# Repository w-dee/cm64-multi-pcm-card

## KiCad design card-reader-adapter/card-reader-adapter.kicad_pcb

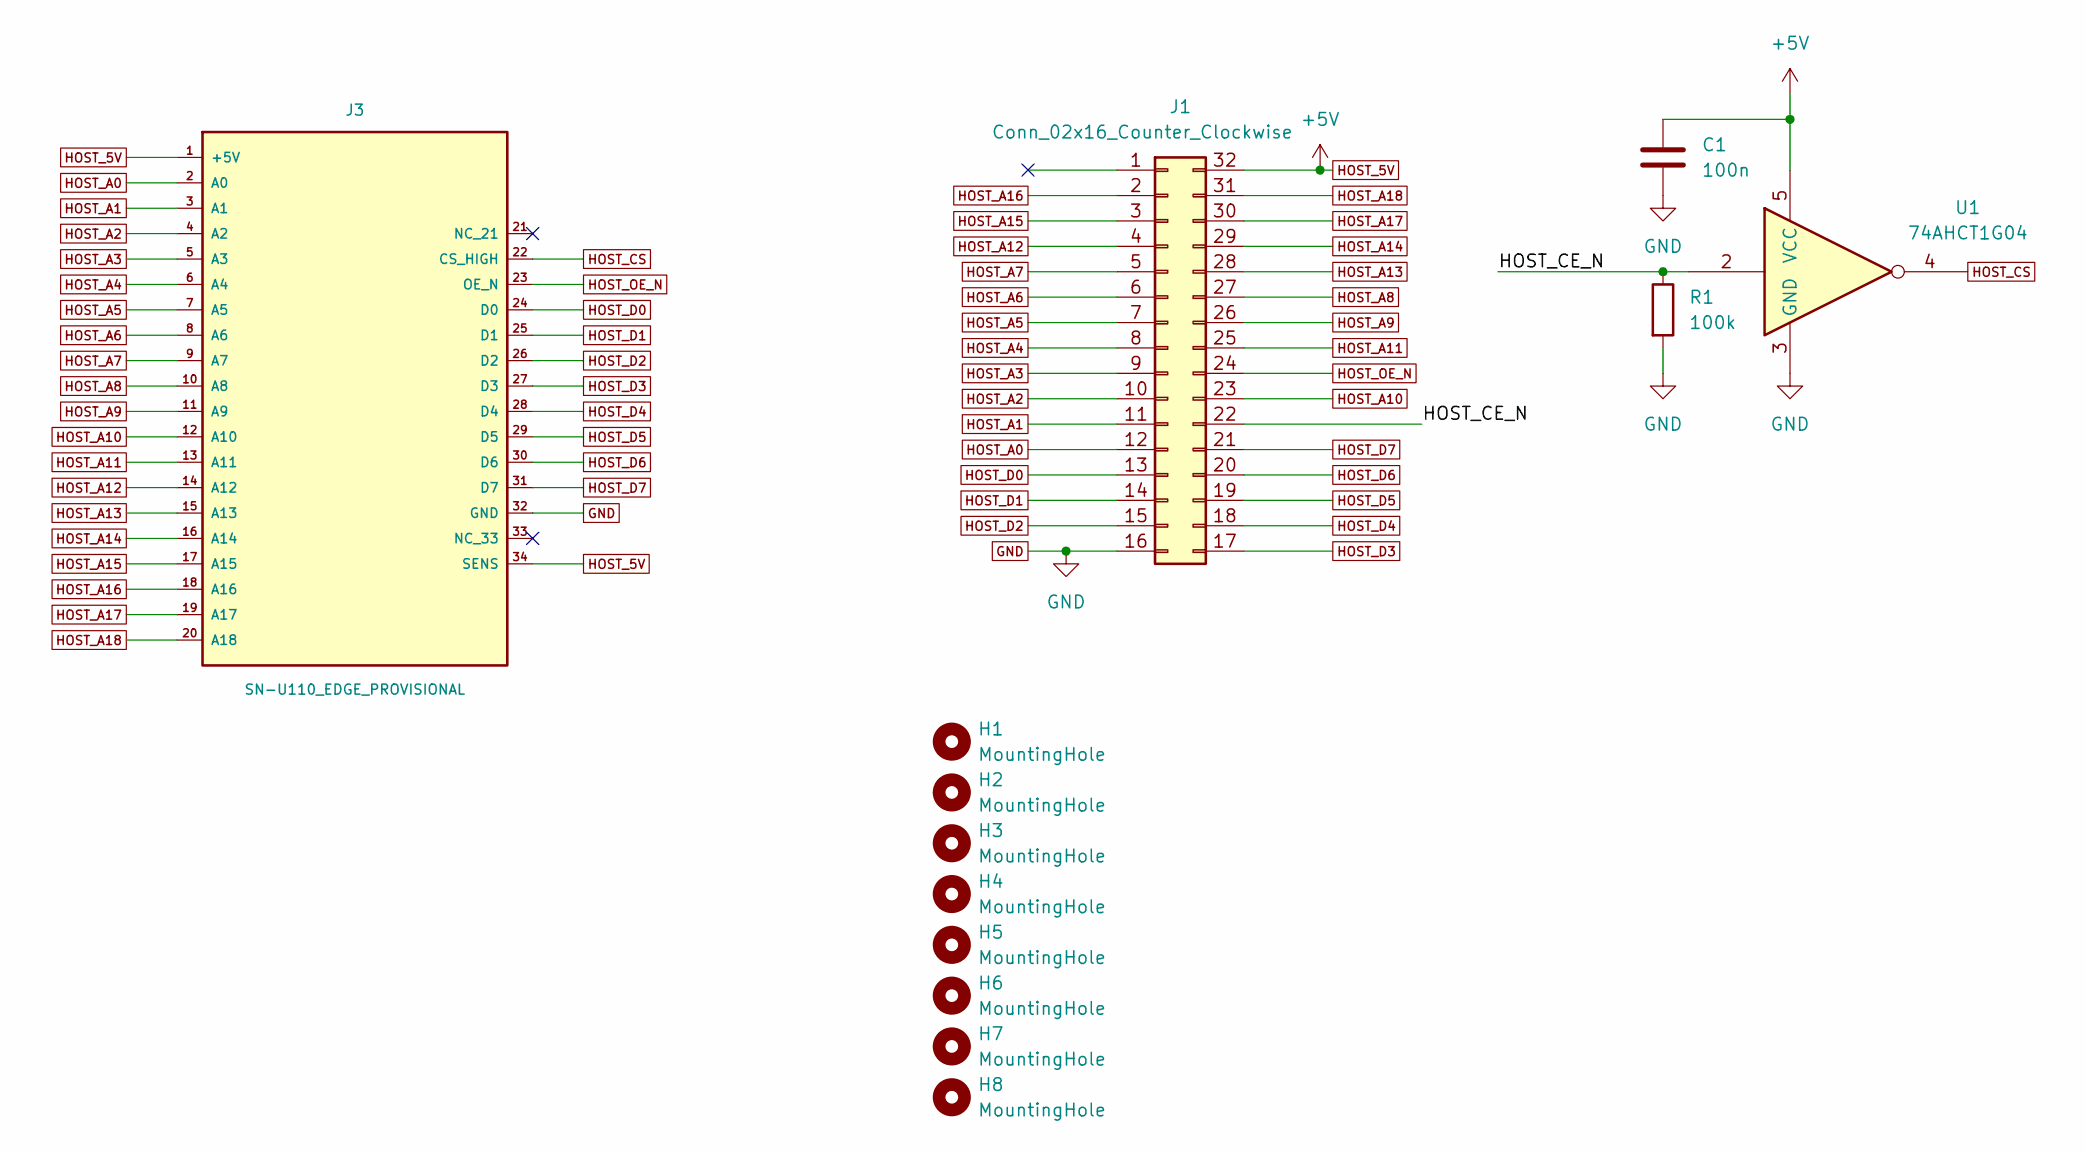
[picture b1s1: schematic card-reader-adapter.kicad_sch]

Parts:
C1: 100n; C_0603_1608Metric_Pad1.08x0.95mm_HandSolder
H1, H2, H3, H4, H5, H6, H7, H8: MountingHole; MountingHole_3.2mm_M3
J1: Conn_02x16_Counter_Clockwise; DIP-32_W15.24mm_Socket_LongPads
J3: SN-U110_EDGE_PROVISIONAL; pogo-pins-SN-U110; MPN SN-U110_EDGE_PROVISIONAL
R1: 100k; R_0603_1608Metric_Pad0.98x0.95mm_HandSolder
U1: 74AHCT1G04; SOT-23-5_HandSoldering

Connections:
/HOST_CE_N: J1.22, R1.1, U1.2
GND: C1.2, J1.16, J3.32 (GND), R1.2, U1.3 (GND)
HOST_5V: C1.1, J1.32, J3.1 (+5V), J3.34 (SENS), U1.5 (VCC)
HOST_A0: J1.12, J3.2 (A0)
HOST_A1: J1.11, J3.3 (A1)
HOST_A2: J1.10, J3.4 (A2)
HOST_A3: J1.9, J3.5 (A3)
HOST_A4: J1.8, J3.6 (A4)
HOST_A5: J1.7, J3.7 (A5)
HOST_A6: J1.6, J3.8 (A6)
HOST_A7: J1.5, J3.9 (A7)
HOST_A8: J1.27, J3.10 (A8)
HOST_A9: J1.26, J3.11 (A9)
HOST_A10: J1.23, J3.12 (A10)
HOST_A11: J1.25, J3.13 (A11)
HOST_A12: J1.4, J3.14 (A12)
HOST_A13: J1.28, J3.15 (A13)
HOST_A14: J1.29, J3.16 (A14)
HOST_A15: J1.3, J3.17 (A15)
HOST_A16: J1.2, J3.18 (A16)
HOST_A17: J1.30, J3.19 (A17)
HOST_A18: J1.31, J3.20 (A18)
HOST_CS: J3.22 (CS_HIGH), U1.4
HOST_D0: J1.13, J3.24 (D0)
HOST_D1: J1.14, J3.25 (D1)
HOST_D2: J1.15, J3.26 (D2)
HOST_D3: J1.17, J3.27 (D3)
HOST_D4: J1.18, J3.28 (D4)
HOST_D5: J1.19, J3.29 (D5)
HOST_D6: J1.20, J3.30 (D6)
HOST_D7: J1.21, J3.31 (D7)
HOST_OE_N: J1.24, J3.23 (OE_N)

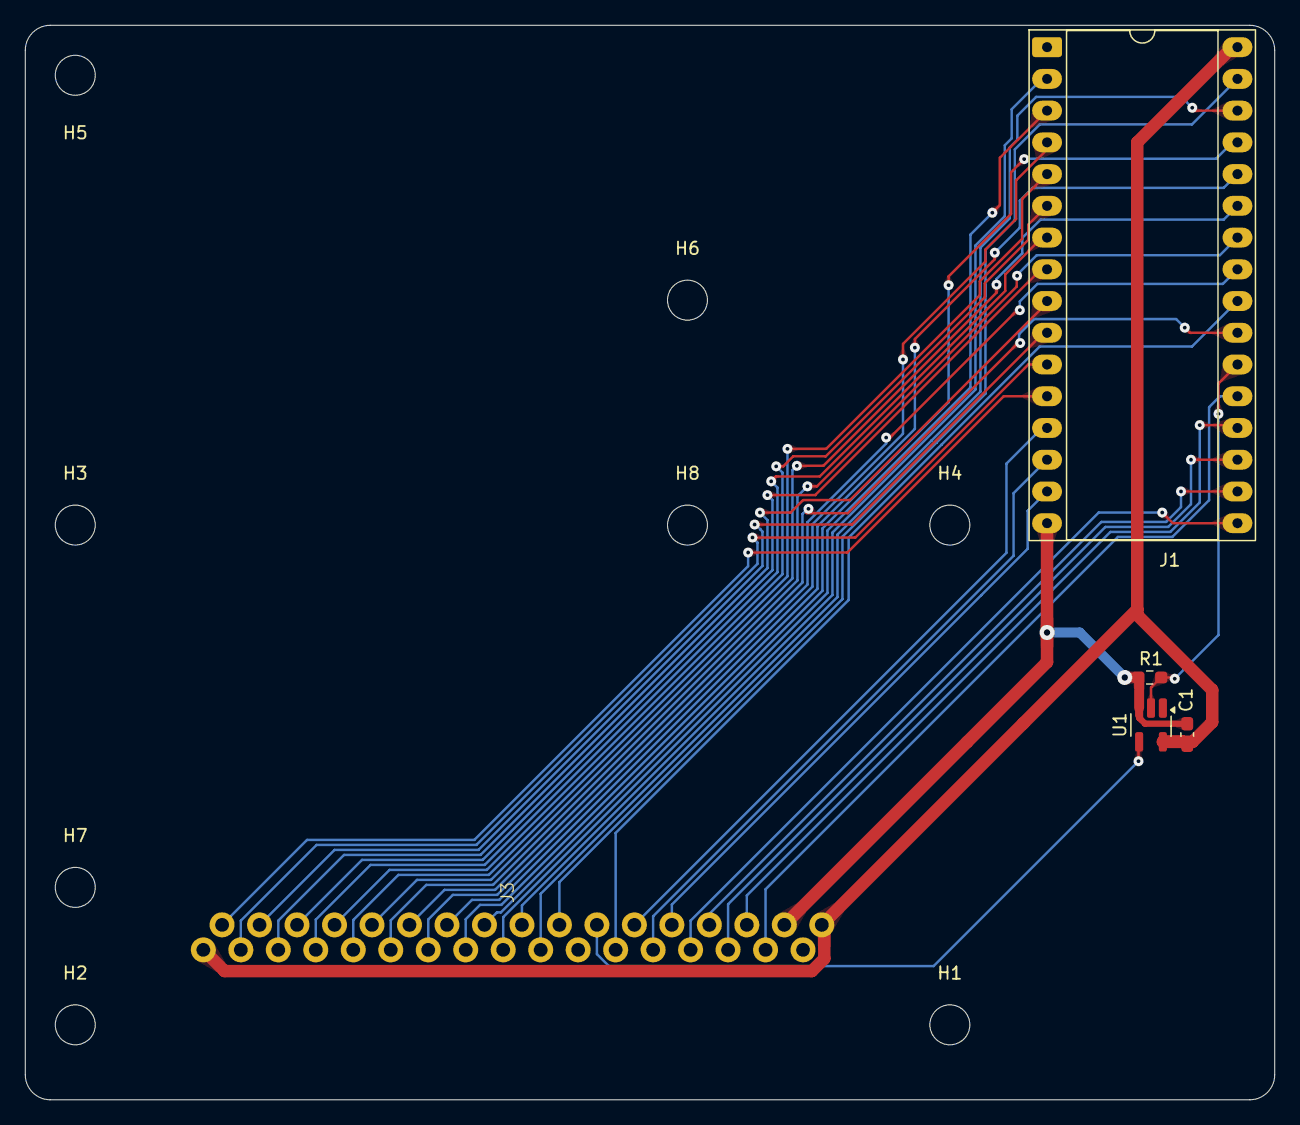
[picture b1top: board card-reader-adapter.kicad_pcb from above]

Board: 2 copper layers, 100.0 x 86.0 mm, 13 parts (0 on the bottom side), 32 nets.

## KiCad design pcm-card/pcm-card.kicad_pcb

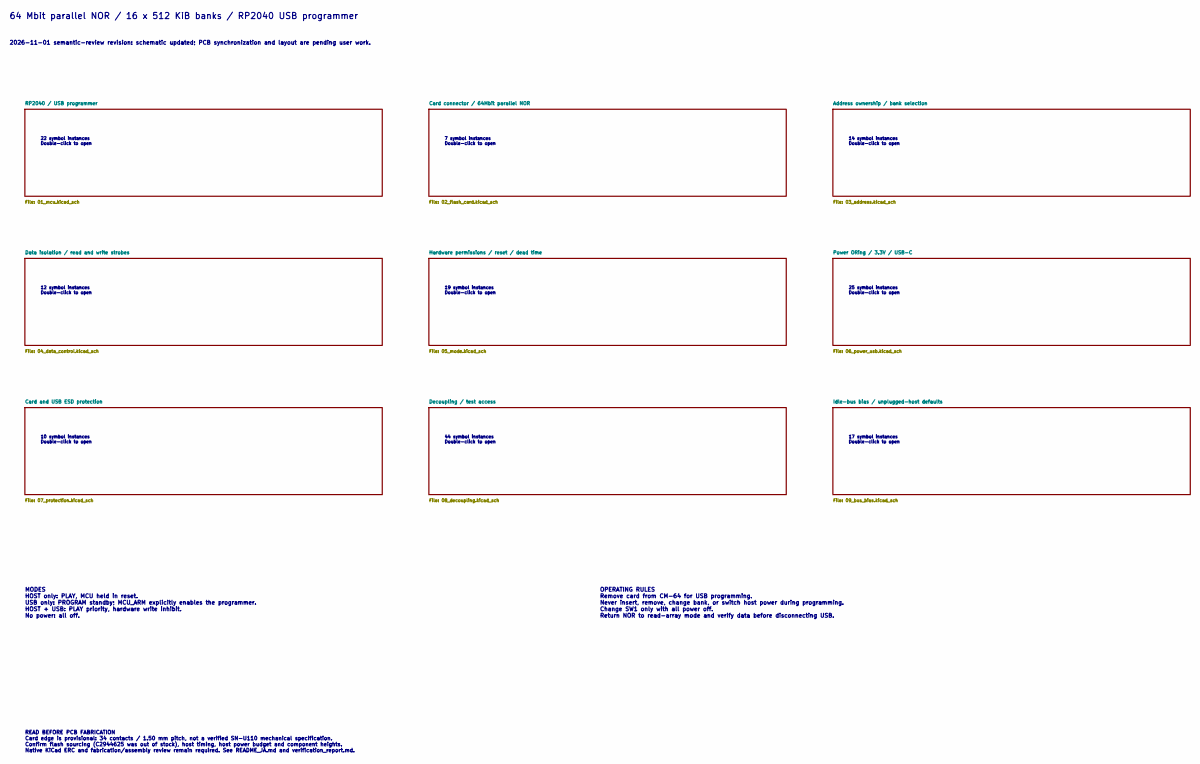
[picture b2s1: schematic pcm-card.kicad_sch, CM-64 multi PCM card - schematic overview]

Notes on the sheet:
22 symbol instances Double-click to open
12 symbol instances Double-click to open
17 symbol instances Double-click to open
7 symbol instances Double-click to open
44 symbol instances Double-click to open
10 symbol instances Double-click to open
14 symbol instances Double-click to open
25 symbol instances Double-click to open
2026-11-01 semantic-review revision: schematic updated; PCB synchronization and layout are pending user work.
OPERATING RULES Remove card from CM-64 for USB programming. Never insert, remove, change bank, or switch host power during programming. Change SW1 only with all power off. Return NOR to read-array mode and verify data before disconnecting USB.
64 Mbit parallel NOR / 16 x 512 KiB banks / RP2040 USB programmer
READ BEFORE PCB FABRICATION Card edge is provisional: 34 contacts / 1.50 mm pitch, not a verified SN-U110 mechanical specification. Confirm flash sourcing (C2944625 was out of stock), host timing, host power budget and component heights. Native KiCad ERC and fabrication/assembly review remain requi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
MODES HOST only: PLAY, MCU held in reset. USB only: PROGRAM standby; MCU_ARM explicitly enables the programmer. HOST + USB: PLAY priority, hardware write inhibit. No power: all off.
19 symbol instances Double-click to open

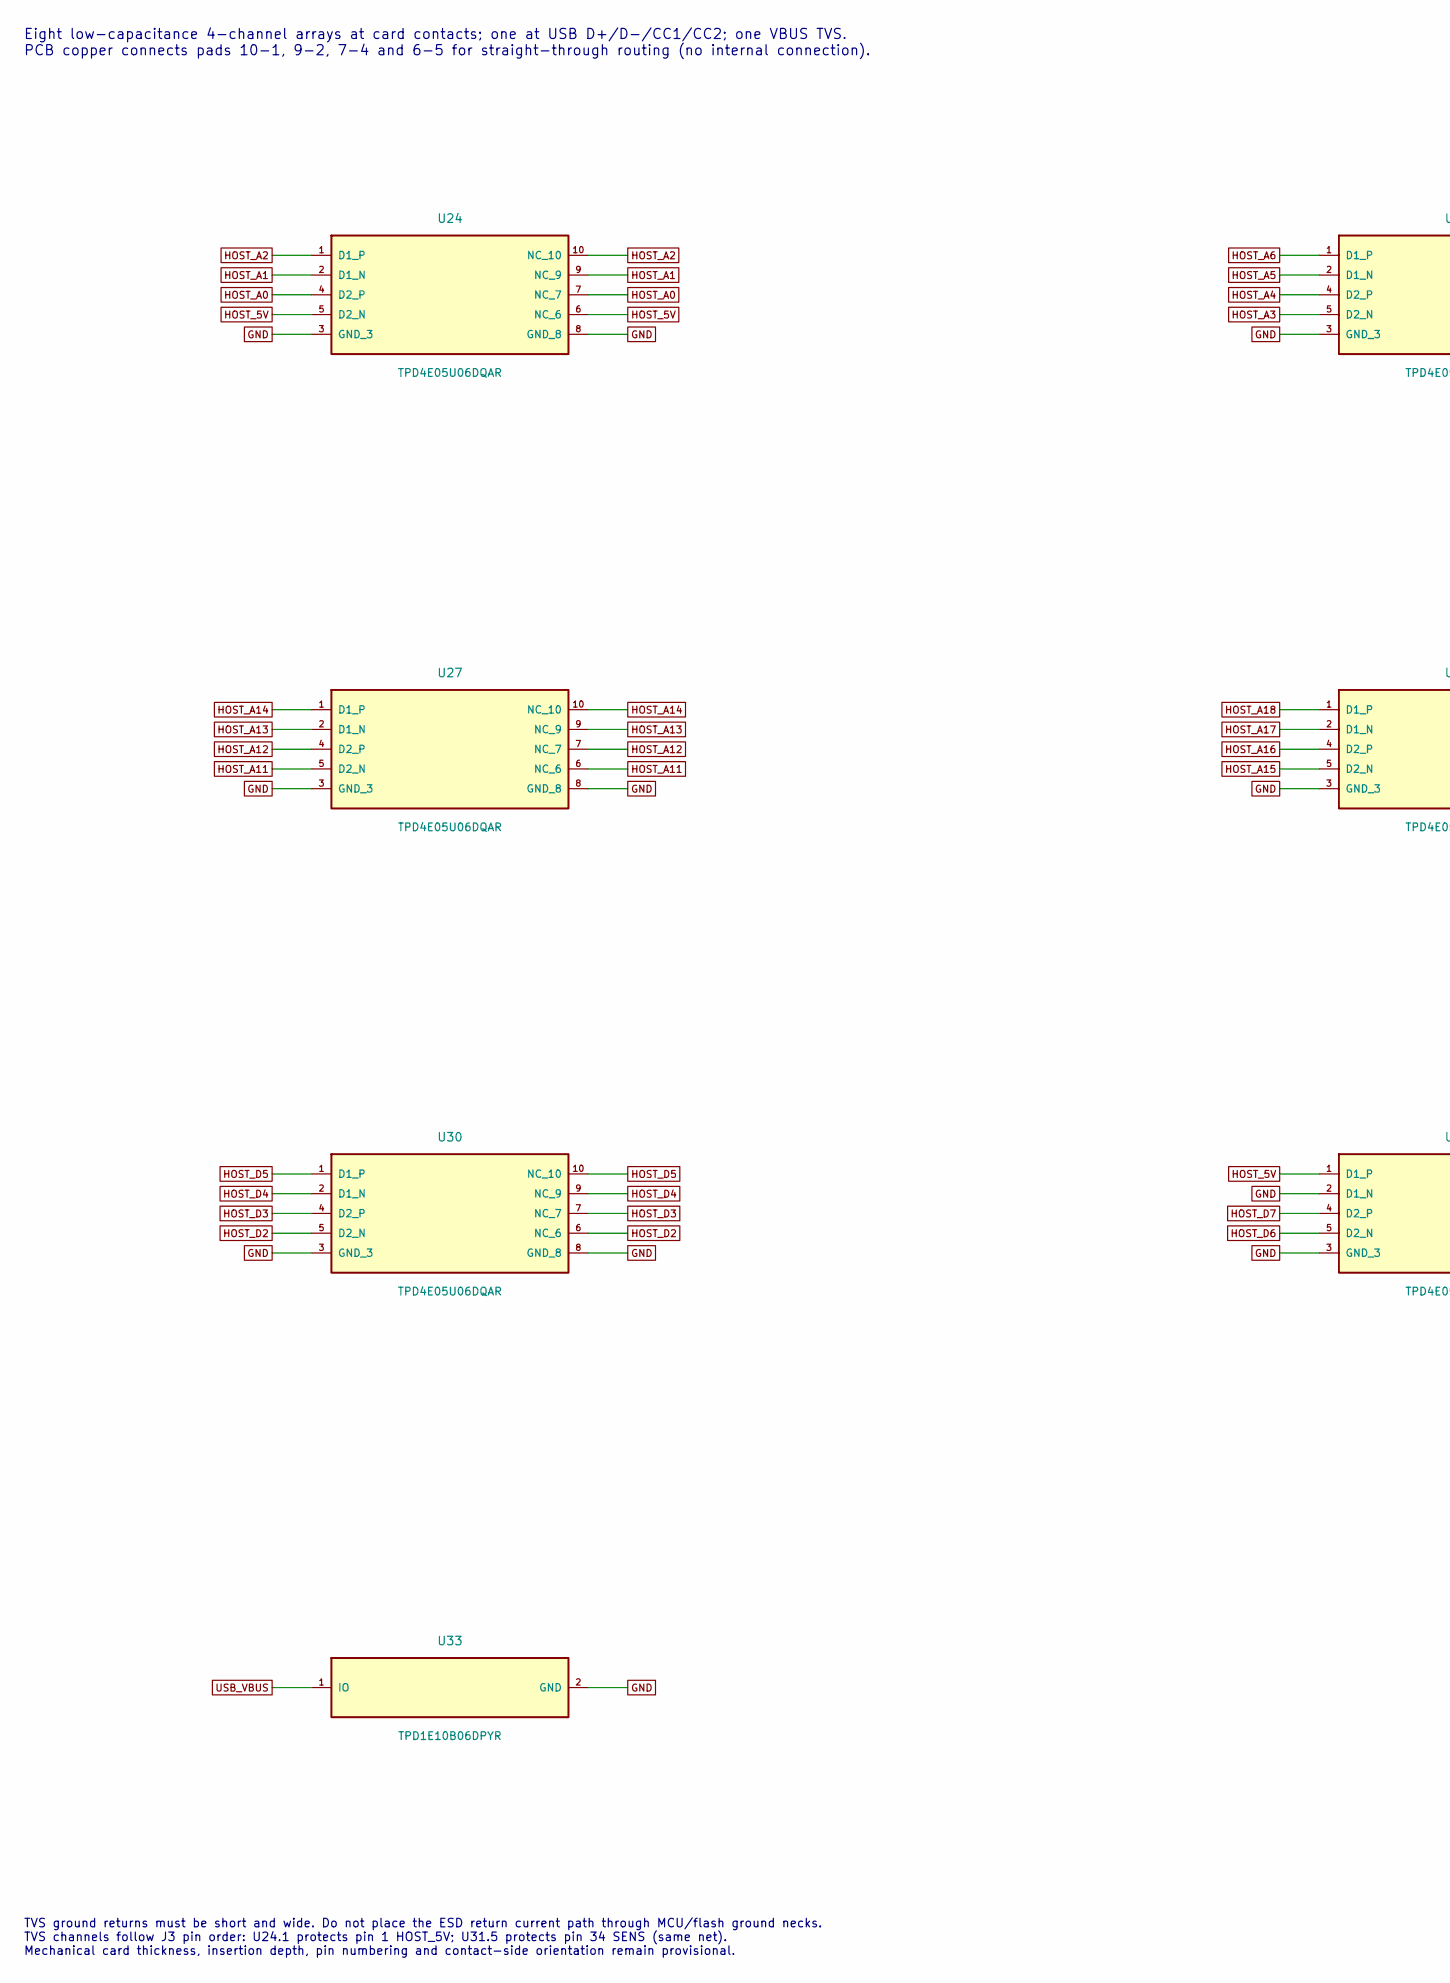
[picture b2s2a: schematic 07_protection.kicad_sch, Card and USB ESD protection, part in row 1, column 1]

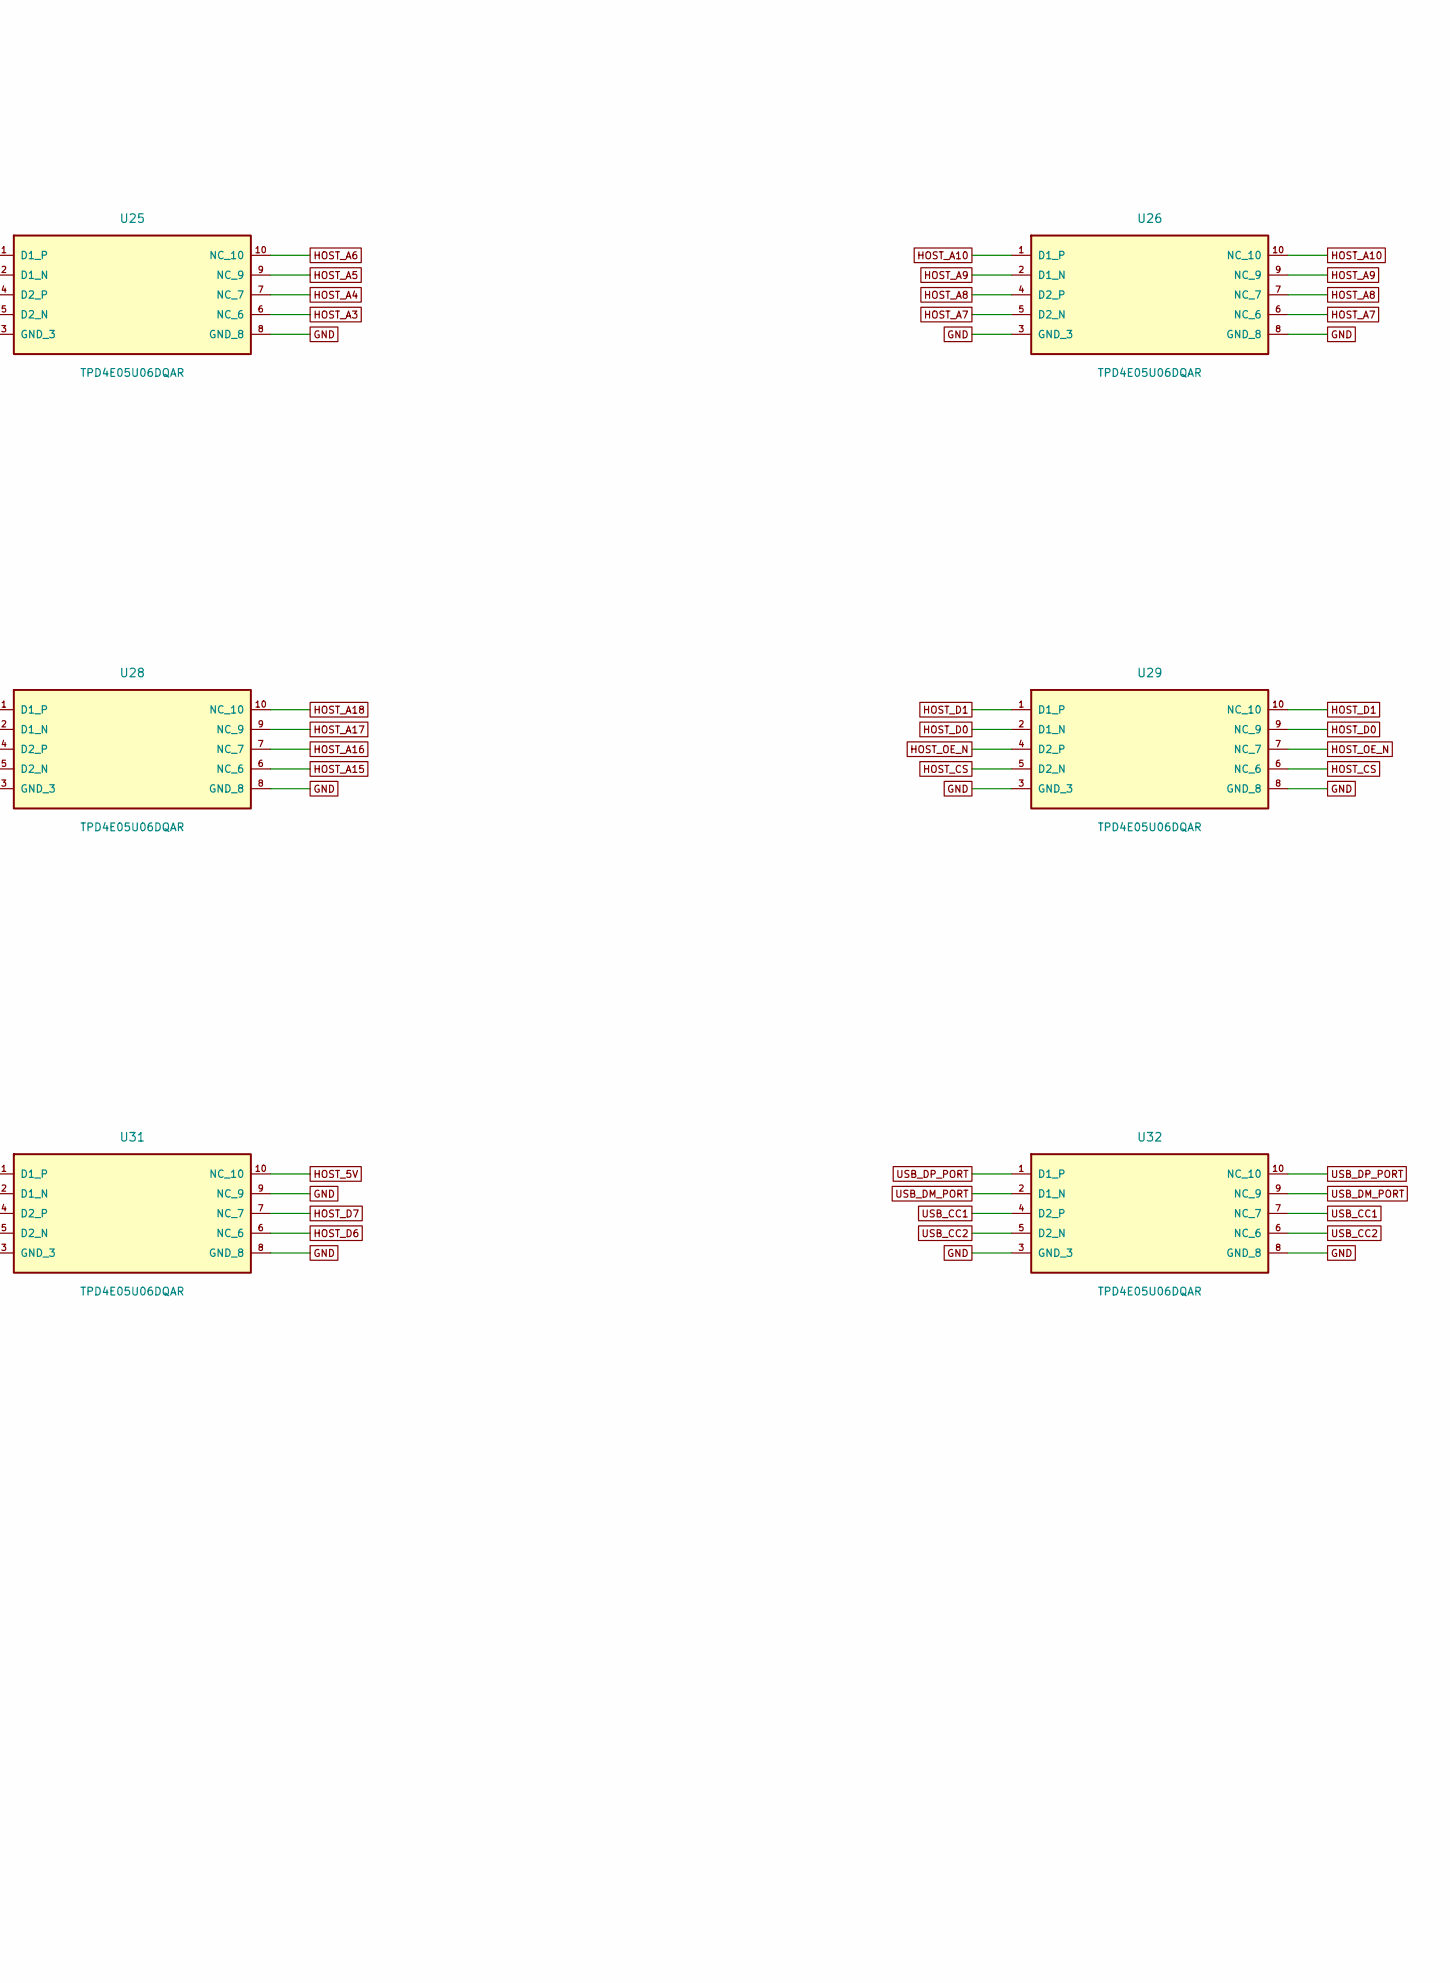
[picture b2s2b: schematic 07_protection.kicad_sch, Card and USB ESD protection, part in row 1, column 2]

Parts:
U24, U25, U26, U27, U28, U29, U30, U31, U32: TPD4E05U06DQAR; USON-10_2.5x1_P0.5; MPN TPD4E05U06DQAR; LCSC C138714
U33: TPD1E10B06DPYR; X1SON-2_1x0.6; MPN TPD1E10B06DPYR; LCSC C48260

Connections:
GND: U24.3 (GND_3), U24.8 (GND_8), U25.3 (GND_3), U25.8 (GND_8), U26.3 (GND_3), U26.8 (GND_8), U27.3 (GND_3), U27.8 (GND_8), U28.3 (GND_3), U28.8 (GND_8), U29.3 (GND_3), U29.8 (GND_8), U30.3 (GND_3), U30.8 (GND_8), U31.2 (D1_N), U31.3 (GND_3), U31.8 (GND_8), U31.9 (NC_9), U32.3 (GND_3), U32.8 (GND_8), U33.2 (GND); also elsewhere on the board
HOST_5V: U24.5 (D2_N), U24.6 (NC_6), U31.1 (D1_P), U31.10 (NC_10); also elsewhere on the board
HOST_A0: U24.4 (D2_P), U24.7 (NC_7); also elsewhere on the board
HOST_A1: U24.2 (D1_N), U24.9 (NC_9); also elsewhere on the board
HOST_A2: U24.1 (D1_P), U24.10 (NC_10); also elsewhere on the board
HOST_A3: U25.5 (D2_N), U25.6 (NC_6); also elsewhere on the board
HOST_A4: U25.4 (D2_P), U25.7 (NC_7); also elsewhere on the board
HOST_A5: U25.2 (D1_N), U25.9 (NC_9); also elsewhere on the board
HOST_A6: U25.1 (D1_P), U25.10 (NC_10); also elsewhere on the board
HOST_A7: U26.5 (D2_N), U26.6 (NC_6); also elsewhere on the board
HOST_A8: U26.4 (D2_P), U26.7 (NC_7); also elsewhere on the board
HOST_A9: U26.2 (D1_N), U26.9 (NC_9); also elsewhere on the board
HOST_A10: U26.1 (D1_P), U26.10 (NC_10); also elsewhere on the board
HOST_A11: U27.5 (D2_N), U27.6 (NC_6); also elsewhere on the board
HOST_A12: U27.4 (D2_P), U27.7 (NC_7); also elsewhere on the board
HOST_A13: U27.2 (D1_N), U27.9 (NC_9); also elsewhere on the board
HOST_A14: U27.1 (D1_P), U27.10 (NC_10); also elsewhere on the board
HOST_A15: U28.5 (D2_N), U28.6 (NC_6); also elsewhere on the board
HOST_A16: U28.4 (D2_P), U28.7 (NC_7); also elsewhere on the board
HOST_A17: U28.2 (D1_N), U28.9 (NC_9); also elsewhere on the board
HOST_A18: U28.1 (D1_P), U28.10 (NC_10); also elsewhere on the board
HOST_CS: U29.5 (D2_N), U29.6 (NC_6); also elsewhere on the board
HOST_D0: U29.2 (D1_N), U29.9 (NC_9); also elsewhere on the board
HOST_D1: U29.1 (D1_P), U29.10 (NC_10); also elsewhere on the board
HOST_D2: U30.5 (D2_N), U30.6 (NC_6); also elsewhere on the board
HOST_D3: U30.4 (D2_P), U30.7 (NC_7); also elsewhere on the board
HOST_D4: U30.2 (D1_N), U30.9 (NC_9); also elsewhere on the board
HOST_D5: U30.1 (D1_P), U30.10 (NC_10); also elsewhere on the board
HOST_D6: U31.5 (D2_N), U31.6 (NC_6); also elsewhere on the board
HOST_D7: U31.4 (D2_P), U31.7 (NC_7); also elsewhere on the board
HOST_OE_N: U29.4 (D2_P), U29.7 (NC_7); also elsewhere on the board
USB_CC1: U32.4 (D2_P), U32.7 (NC_7); also elsewhere on the board
USB_CC2: U32.5 (D2_N), U32.6 (NC_6); also elsewhere on the board
USB_DM_PORT: U32.2 (D1_N), U32.9 (NC_9); also elsewhere on the board
USB_DP_PORT: U32.1 (D1_P), U32.10 (NC_10); also elsewhere on the board
USB_VBUS: U33.1 (IO); also elsewhere on the board

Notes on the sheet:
Eight low-capacitance 4-channel arrays at card contacts; one at USB D+/D-/CC1/CC2; one VBUS TVS. PCB copper connects pads 10-1, 9-2, 7-4 and 6-5 for straight-through routing (no internal connection).
TVS ground returns must be short and wide. Do not place the ESD return current path through MCU/flash ground necks. TVS channels follow J3 pin order: U24.1 protects pin 1 HOST_5V; U31.5 protects pin 34 SENS (same net). Mechanical card thickness, insertion depth, pin numbering and contact-side orien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

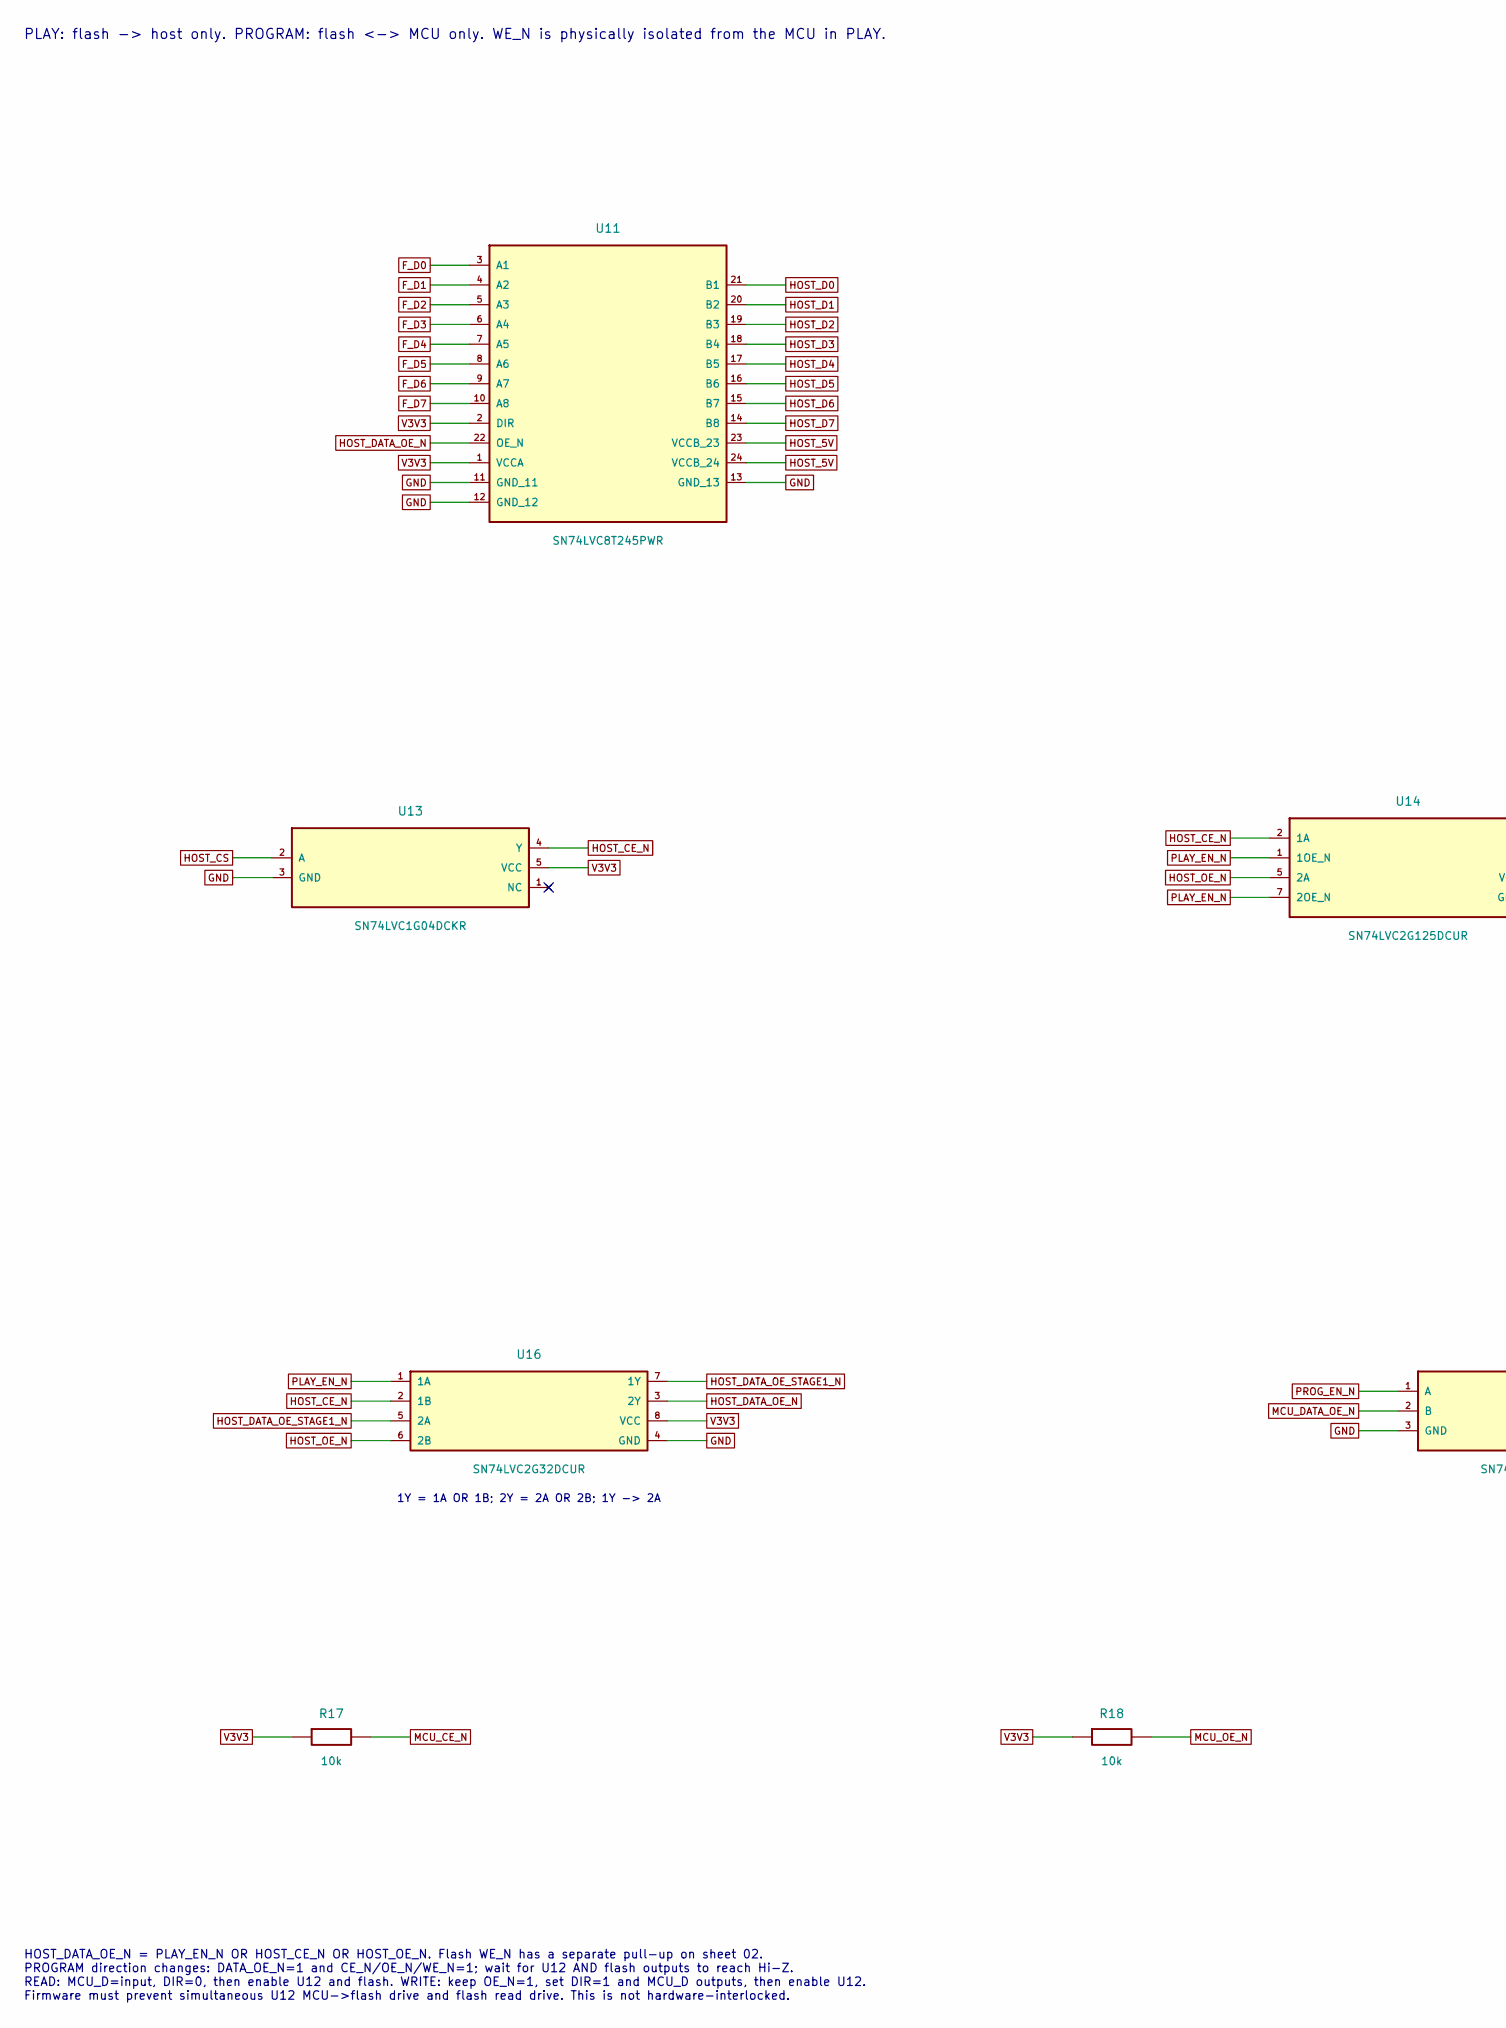
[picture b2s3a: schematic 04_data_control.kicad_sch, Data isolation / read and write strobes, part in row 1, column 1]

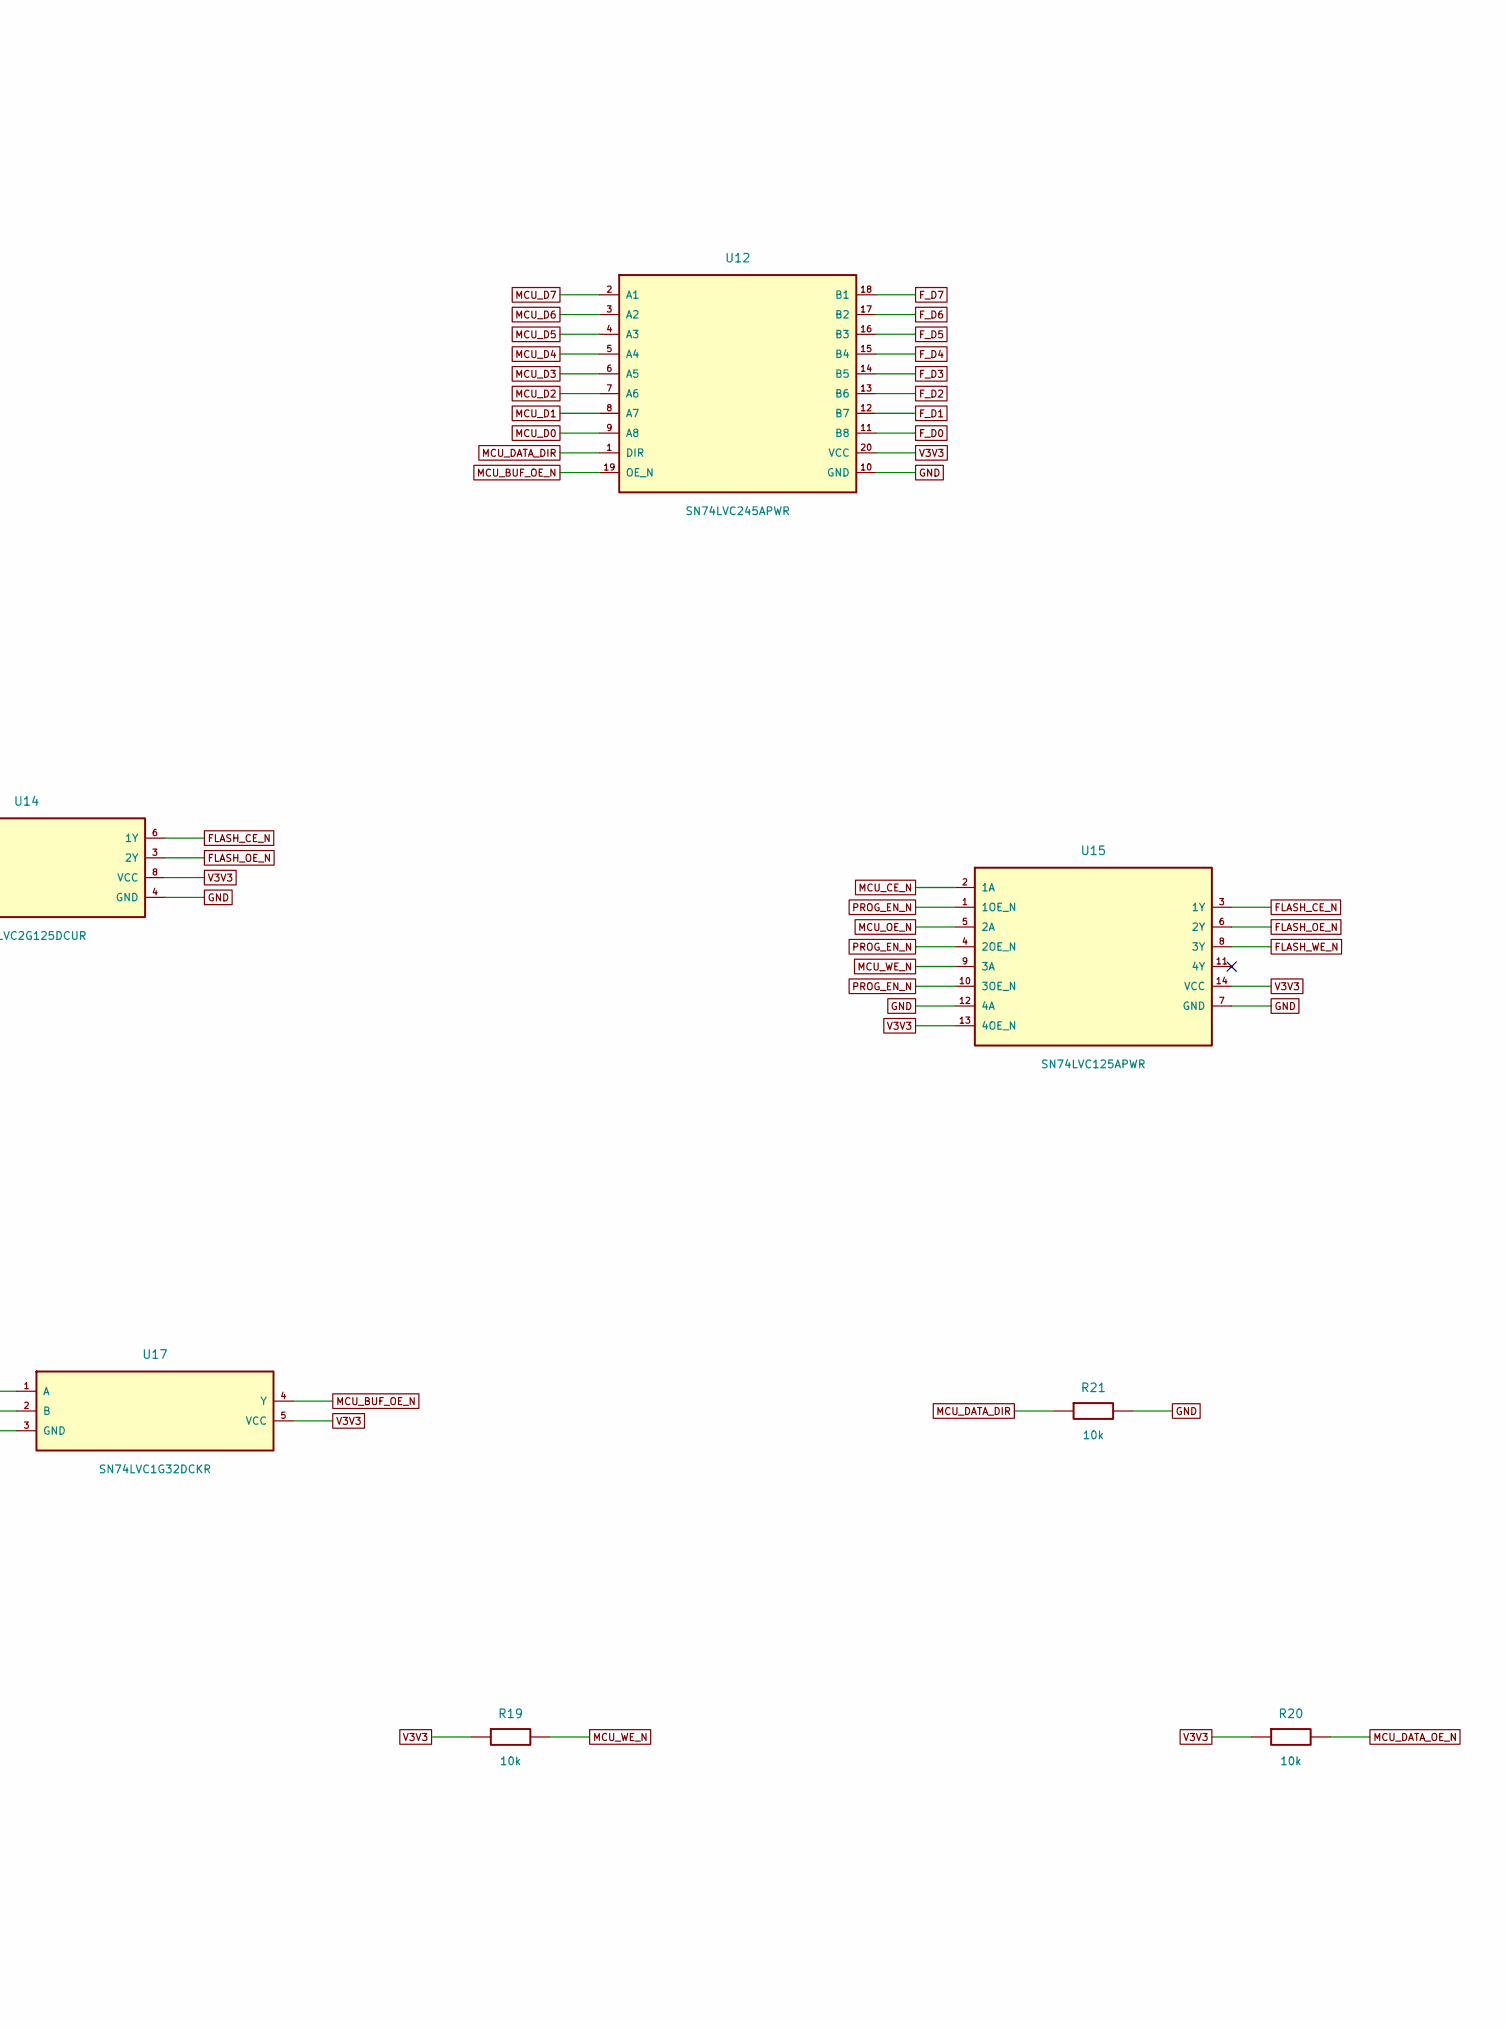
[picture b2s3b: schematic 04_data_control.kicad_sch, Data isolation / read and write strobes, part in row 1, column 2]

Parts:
R17, R18, R19, R20, R21: 10k; R_0603_1608Metric; MPN 0603WAF1002T5E; LCSC C25804
U11: SN74LVC8T245PWR; TSSOP-24_4.4x7.8_P0.65; MPN SN74LVC8T245PWR; LCSC C27643
U12: SN74LVC245APWR; TSSOP-20_4.4x6.5_P0.65; MPN SN74LVC245APWR; LCSC C7848
U13: SN74LVC1G04DCKR; SC70-5; MPN SN74LVC1G04DCKR; LCSC C8207
U14: SN74LVC2G125DCUR; TI_VSSOP-8_2.3x2mm_P0.5mm; MPN SN74LVC2G125DCUR; LCSC C21404
U15: SN74LVC125APWR; TSSOP-14_4.4x5_P0.65; MPN SN74LVC125APWR; LCSC C7813
U16: SN74LVC2G32DCUR; TI_VSSOP-8_2.3x2mm_P0.5mm; MPN SN74LVC2G32DCUR; LCSC C91874
U17: SN74LVC1G32DCKR; SC70-5; MPN SN74LVC1G32DCKR; LCSC C7840

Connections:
FLASH_CE_N: U14.6 (1Y), U15.3 (1Y); also elsewhere on the board
FLASH_OE_N: U14.3 (2Y), U15.6 (2Y); also elsewhere on the board
FLASH_WE_N: U15.8 (3Y); also elsewhere on the board
F_D0: U11.3 (A1), U12.11 (B8); also elsewhere on the board
F_D1: U11.4 (A2), U12.12 (B7); also elsewhere on the board
F_D2: U11.5 (A3), U12.13 (B6); also elsewhere on the board
F_D3: U11.6 (A4), U12.14 (B5); also elsewhere on the board
F_D4: U11.7 (A5), U12.15 (B4); also elsewhere on the board
F_D5: U11.8 (A6), U12.16 (B3); also elsewhere on the board
F_D6: U11.9 (A7), U12.17 (B2); also elsewhere on the board
F_D7: U11.10 (A8), U12.18 (B1); also elsewhere on the board
GND: R21.2, U11.11 (GND_11), U11.12 (GND_12), U11.13 (GND_13), U12.10 (GND), U13.3 (GND), U14.4 (GND), U15.7 (GND), U15.12 (4A), U16.4 (GND), U17.3 (GND); also elsewhere on the board
HOST_5V: U11.23 (VCCB_23), U11.24 (VCCB_24); also elsewhere on the board
HOST_CE_N: U13.4 (Y), U14.2 (1A), U16.2 (1B)
HOST_CS: U13.2 (A); also elsewhere on the board
HOST_D0: U11.21 (B1); also elsewhere on the board
HOST_D1: U11.20 (B2); also elsewhere on the board
HOST_D2: U11.19 (B3); also elsewhere on the board
HOST_D3: U11.18 (B4); also elsewhere on the board
HOST_D4: U11.17 (B5); also elsewhere on the board
HOST_D5: U11.16 (B6); also elsewhere on the board
HOST_D6: U11.15 (B7); also elsewhere on the board
HOST_D7: U11.14 (B8); also elsewhere on the board
HOST_DATA_OE_N: U11.22 (OE_N), U16.3 (2Y); also elsewhere on the board
HOST_DATA_OE_STAGE1_N: U16.5 (2A), U16.7 (1Y)
HOST_OE_N: U14.5 (2A), U16.6 (2B); also elsewhere on the board
MCU_BUF_OE_N: U12.19 (OE_N), U17.4 (Y); also elsewhere on the board
MCU_CE_N: R17.2, U15.2 (1A); also elsewhere on the board
MCU_D0: U12.9 (A8); also elsewhere on the board
MCU_D1: U12.8 (A7); also elsewhere on the board
MCU_D2: U12.7 (A6); also elsewhere on the board
MCU_D3: U12.6 (A5); also elsewhere on the board
MCU_D4: U12.5 (A4); also elsewhere on the board
MCU_D5: U12.4 (A3); also elsewhere on the board
MCU_D6: U12.3 (A2); also elsewhere on the board
MCU_D7: U12.2 (A1); also elsewhere on the board
MCU_DATA_DIR: R21.1, U12.1 (DIR); also elsewhere on the board
MCU_DATA_OE_N: R20.2, U17.2 (B); also elsewhere on the board
MCU_OE_N: R18.2, U15.5 (2A); also elsewhere on the board
MCU_WE_N: R19.2, U15.9 (3A); also elsewhere on the board
PLAY_EN_N: U14.1 (1OE_N), U14.7 (2OE_N), U16.1 (1A); also elsewhere on the board
PROG_EN_N: U15.1 (1OE_N), U15.4 (2OE_N), U15.10 (3OE_N), U17.1 (A); also elsewhere on the board
V3V3: R17.1, R18.1, R19.1, R20.1, U11.1 (VCCA), U11.2 (DIR), U12.20 (VCC), U13.5 (VCC), U14.8 (VCC), U15.13 (4OE_N), U15.14 (VCC), U16.8 (VCC), U17.5 (VCC); also elsewhere on the board

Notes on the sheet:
HOST_DATA_OE_N = PLAY_EN_N OR HOST_CE_N OR HOST_OE_N. Flash WE_N has a separate pull-up on sheet 02. PROGRAM direction changes: DATA_OE_N=1 and CE_N/OE_N/WE_N=1; wait for U12 AND flash outputs to reach Hi-Z. READ: MCU_D=input, DIR=0, then enable U12 and flash. WRITE: keep OE_N=1, set DIR=1 and MCU_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
PLAY: flash -> host only. PROGRAM: flash <-> MCU only. WE_N is physically isolated from the MCU in PLAY.
1Y = 1A OR 1B; 2Y = 2A OR 2B; 1Y -> 2A
